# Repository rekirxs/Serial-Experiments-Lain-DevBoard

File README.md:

# Serial-Experiments-Lain-DevBoard

let's all love lain.

A custom ESP32-C3 dev board built as a appreciation  to Serial Experiments Lain. Not a Lain branded case for a stock dev board  this is a from-scratch PCB with its own connector layout, onboard RGB status LED, and just enough buttons to feel like a piece of hardware from the Wired.

Also I just wanted an excuse to build a PCB.

Hardware
MCU: ESP32-C3 — WiFi/BLE, RISC-V single-core, low power draw for anything battery-powered
USB-C: native USB-C receptacle (16-pin), no more digging through a drawer for the right cable
Status LED: onboard SK6812 addressable RGB — Present indicator, whatever color the Wired feels like that day
Buttons: 2x SMD tactile switches, low-profile, doesn't add bulk to the silhouette
Power: 3.3V regulated, USB-powered or battery-ready depending on the build

Full BOM and sourcing notes live in /hardware.

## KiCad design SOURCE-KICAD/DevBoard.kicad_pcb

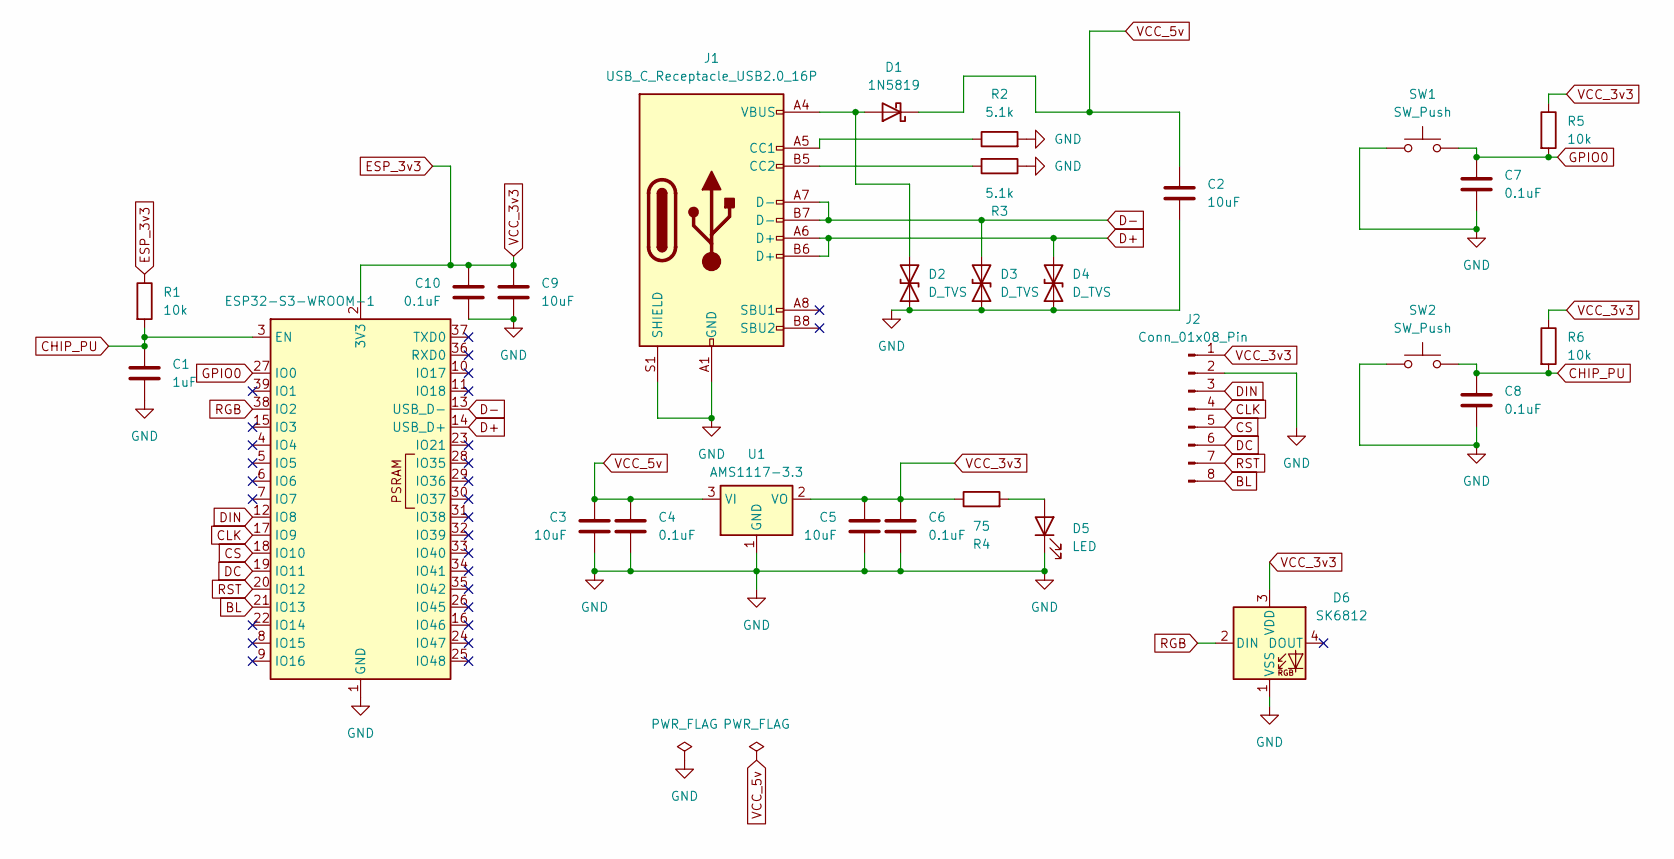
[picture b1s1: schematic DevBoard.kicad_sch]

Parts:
C1: 1uF; C_0805_2012Metric_Pad1.18x1.45mm_HandSolder
C2, C3, C5, C9: 10uF; C_0805_2012Metric_Pad1.18x1.45mm_HandSolder
C4, C6, C7, C8, C10: 0.1uF; C_0805_2012Metric_Pad1.18x1.45mm_HandSolder
D1: 1N5819; D_SOD-123
D2, D3, D4: D_TVS; D_SOD-323_HandSoldering
D5: LED; LED_0805_2012Metric_Pad1.15x1.40mm_HandSolder
D6: SK6812; LED_SK6812_PLCC4_5.0x5.0mm_P3.2mm
J1: USB_C_Receptacle_USB2.0_16P; USB_C_Receptacle_HRO_TYPE-C-31-M-12
J2: Conn_01x08_Pin; PinSocket_1x08_P2.54mm_Vertical
R1, R5, R6: 10k; R_0805_2012Metric_Pad1.20x1.40mm_HandSolder
R2, R3: 5.1k; R_0805_2012Metric_Pad1.20x1.40mm_HandSolder
R4: 75; R_0805_2012Metric_Pad1.20x1.40mm_HandSolder
SW1, SW2: SW_Push; SW_SPST_PTS810
U1: AMS1117-3.3; SOT-223-3_TabPin2
U2: ESP32-S3-WROOM-1; ESP32-S3-WROOM-1U

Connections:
BL: J2.8, U2.21 (IO13)
CHIP_PU: C1.1, C8.1, R1.2, R6.2, SW2.2, U2.3 (EN)
CLK: J2.4, U2.17 (IO9)
CS: J2.5, U2.18 (IO10)
D+: D4.2 (A2), J1.A6 (D+), J1.B6 (D+), U2.14 (USB_D+)
D-: D3.2 (A2), J1.A7 (D-), J1.B7 (D-), U2.13 (USB_D-)
DC: J2.6, U2.19 (IO11)
DIN: J2.3, U2.12 (IO8)
ESP_3v3: C5.1, C6.1, C9.1, C10.1, D6.3 (VDD), J2.1, R1.1, R4.1, R5.1, R6.1, U1.2 (VO), U2.2 (3V3)
GND: C1.2, C2.2, C3.2, C4.2, C5.2, C6.2, C7.2, C8.2, C9.2, C10.2, D2.1 (A1), D3.1 (A1), D4.1 (A1), D5.1 (K), D6.1 (VSS), J1.A1 (GND), J1.A12 (GND), J1.B1 (GND), J1.B12 (GND), J1.S1 (SHIELD), J2.2, R2.2, R3.1, SW1.1, SW2.1, U1.1 (GND), U2.1 (GND), U2.40 (GND), U2.41 (GND)
GPIO0: C7.1, R5.2, SW1.2, U2.27 (IO0)
unnamed: D1.2 (A), D2.2 (A2), J1.A4 (VBUS), J1.A9 (VBUS), J1.B4 (VBUS), J1.B9 (VBUS)
unnamed: D5.2 (A), R4.2
unnamed: J1.A5 (CC1), R2.1
unnamed: J1.B5 (CC2), R3.2
RGB: D6.2 (DIN), U2.38 (IO2)
RST: J2.7, U2.20 (IO12)
VCC_5v: C2.1, C3.1, C4.1, D1.1 (K), U1.3 (VI)

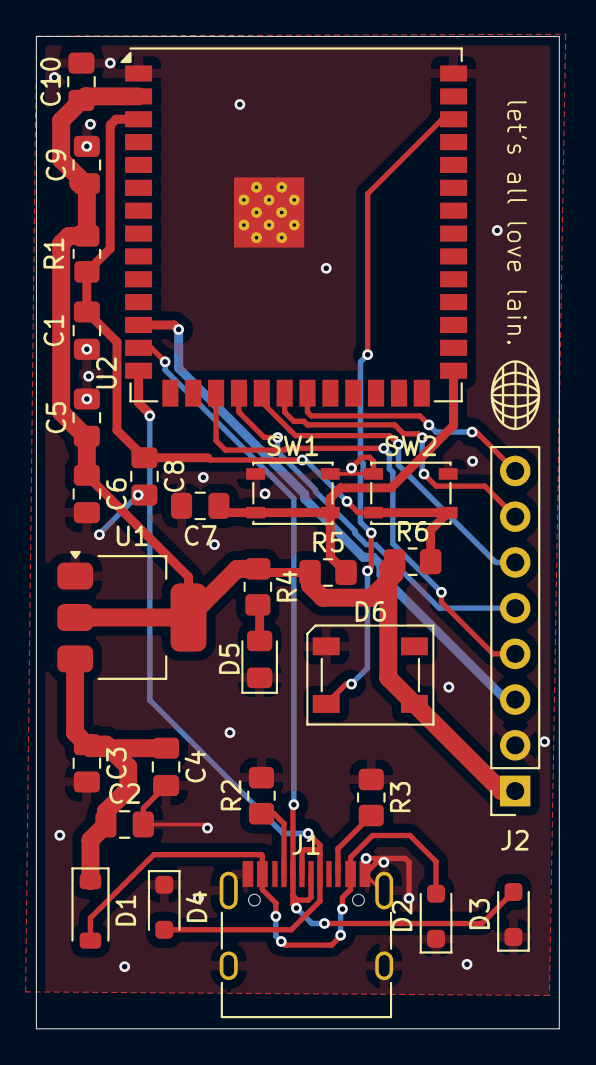
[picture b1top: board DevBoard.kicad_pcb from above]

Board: 2 copper layers, 29.0 x 55.1 mm, 28 parts (0 on the bottom side), 18 nets.

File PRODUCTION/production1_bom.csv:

Designator,Footprint,Quantity,Value,LCSC Part #
C1,0805,1,1uF,
"C10, C4, C6, C7, C8",0805,5,0.1uF,
"C2, C3, C5, C9",0805,4,10uF,
D1,D_SOD-123,1,1N5819,
"D2, D3, D4",D_SOD-323_HandSoldering,3,D_TVS,
D5,0805,1,LED,
D6,LED_SK6812_PLCC4_5.0x5.0mm_P3.2mm,1,SK6812,
J1,USB_C_Receptacle_HRO_TYPE-C-31-M-12,1,USB_C_Receptacle_USB2.0_16P,
J2,PinSocket_1x08_P2.54mm_Vertical,1,Conn_01x08_Pin,
"R1, R5, R6",0805,3,10k,
"R2, R3",0805,2,5.1k,
R4,0805,1,75,
"SW1, SW2",SW_SPST_PTS810,2,SW_Push,
U1,SOT-223-3_TabPin2,1,AMS1117-3.3,
U2,ESP32-S3-WROOM-1U,1,ESP32-S3-WROOM-1,

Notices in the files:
SOURCE-KICAD/DevBoard.kicad_pcb:
©triangle
